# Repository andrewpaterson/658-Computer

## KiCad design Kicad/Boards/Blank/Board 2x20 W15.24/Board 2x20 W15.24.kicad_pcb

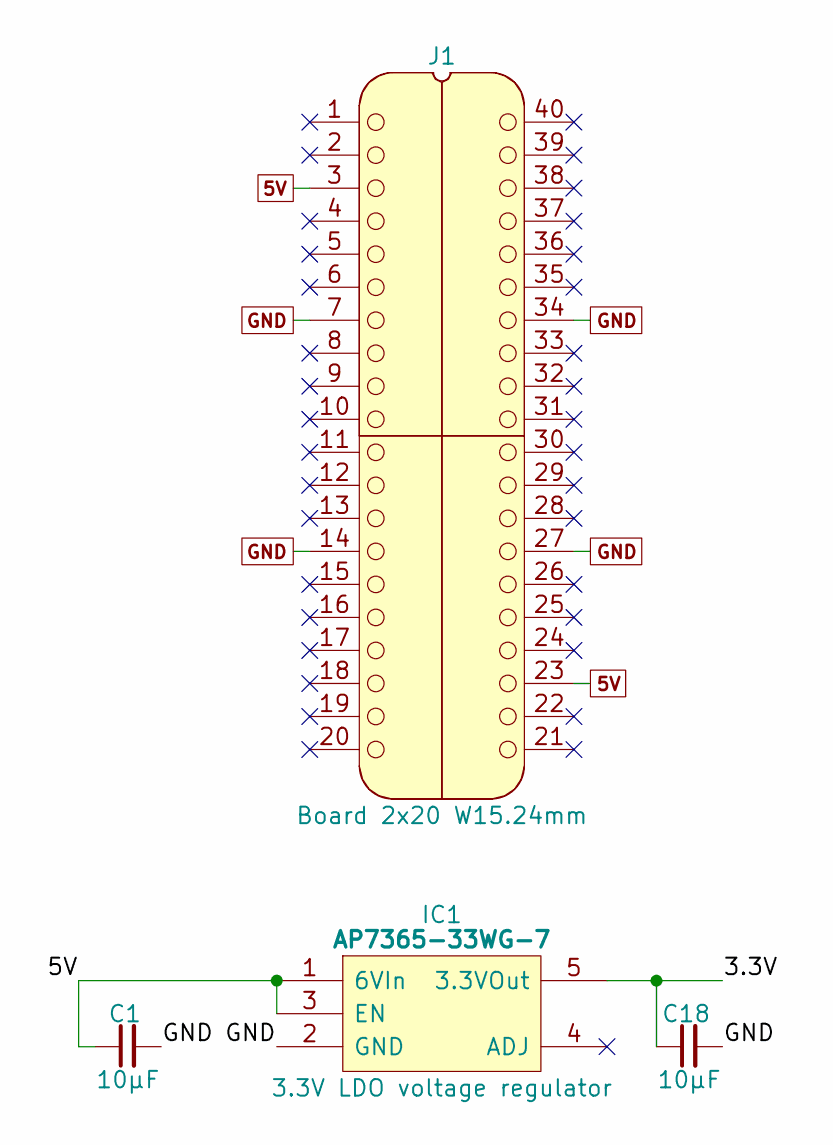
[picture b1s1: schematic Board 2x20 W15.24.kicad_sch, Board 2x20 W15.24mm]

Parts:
C1, C18: 10µF; C_0805
IC1: AP7365-33WG-7; SOT95P285X130-5N; Manufacturer_Part_Number AP7365-33WG-7; Mouser Part Number 621-AP7365-33WG-7
J1: Board 2x20 W15.24mm; DIP-40_Board_W15.24mm

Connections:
5V: C1.1, IC1.1 (6VIn), IC1.3 (EN), J1.3, J1.23
/3.3V: C18.1, IC1.5 (3.3VOut)
GND: C1.2, C18.2, IC1.2 (GND), J1.7, J1.14, J1.27, J1.34

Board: 2 copper layers, 4 parts (0 on the bottom side), 3 nets, no tracks yet.

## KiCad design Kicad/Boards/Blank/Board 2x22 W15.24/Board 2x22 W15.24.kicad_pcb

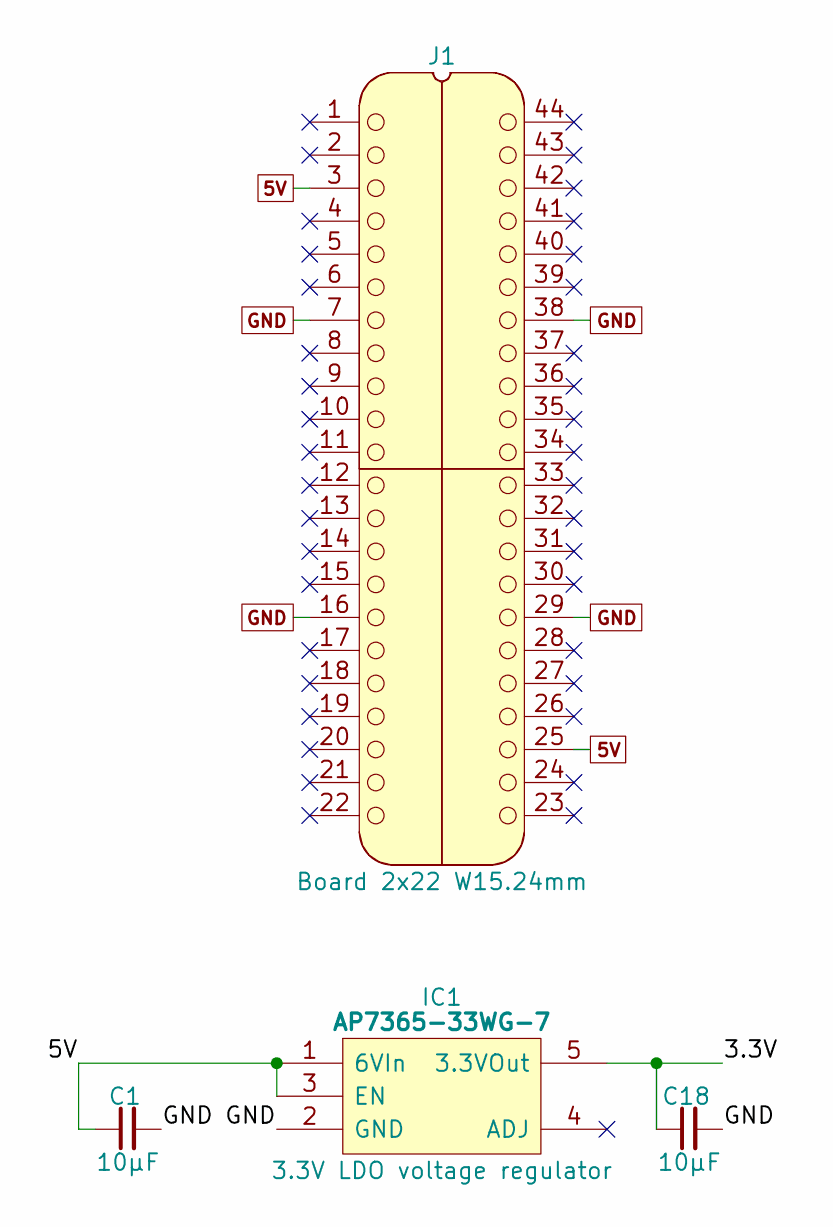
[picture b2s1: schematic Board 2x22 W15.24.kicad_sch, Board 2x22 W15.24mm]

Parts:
C1, C18: 10µF; C_0805
IC1: AP7365-33WG-7; SOT95P285X130-5N; Manufacturer_Part_Number AP7365-33WG-7; Mouser Part Number 621-AP7365-33WG-7
J1: Board 2x22 W15.24mm; DIP-44_Board_W15.24mm

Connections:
5V: C1.1, IC1.1 (6VIn), IC1.3 (EN), J1.3, J1.25
/3.3V: C18.1, IC1.5 (3.3VOut)
GND: C1.2, C18.2, IC1.2 (GND), J1.7, J1.16, J1.29, J1.38

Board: 2 copper layers, 4 parts (0 on the bottom side), 3 nets, no tracks yet.

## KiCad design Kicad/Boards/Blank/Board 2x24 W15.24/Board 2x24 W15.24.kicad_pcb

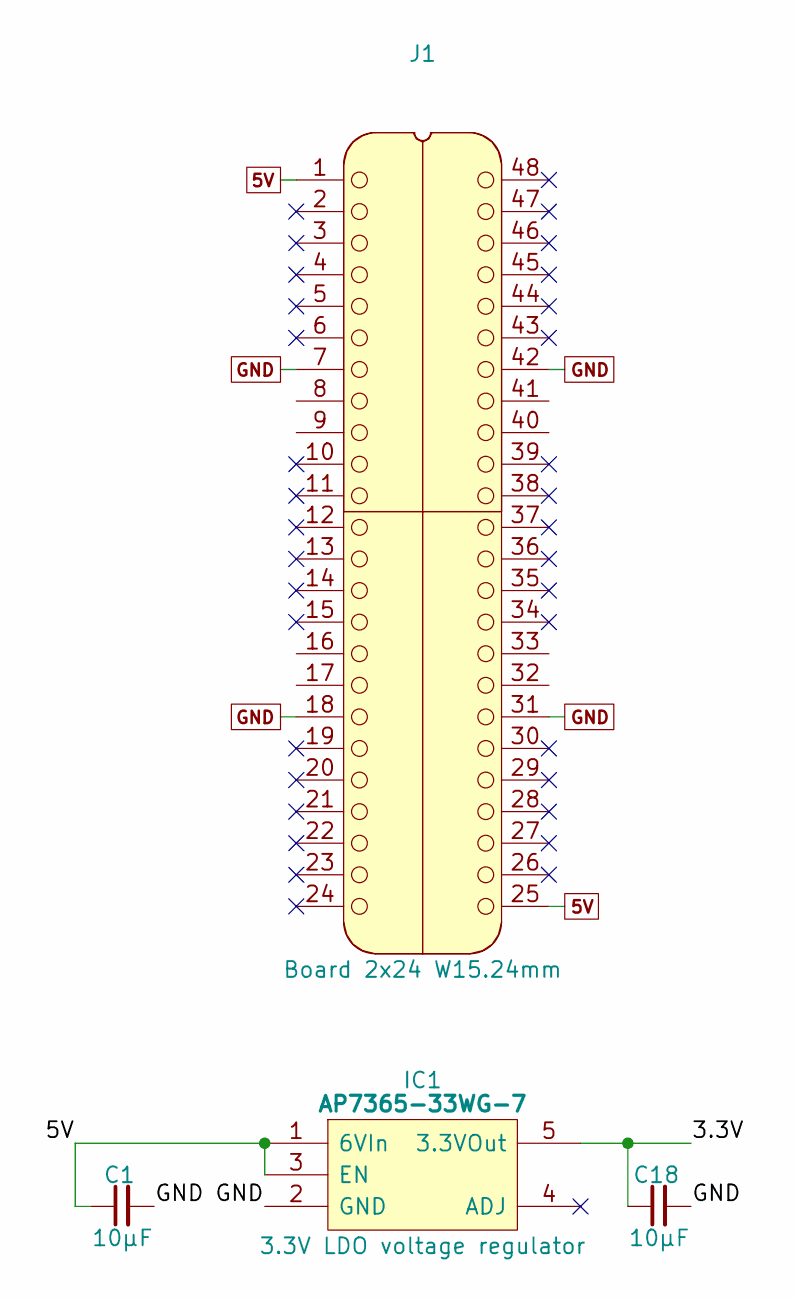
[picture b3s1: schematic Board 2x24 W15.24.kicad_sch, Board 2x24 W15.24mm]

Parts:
C1, C18: 10µF; C_0805
IC1: AP7365-33WG-7; SOT95P285X130-5N; Manufacturer_Part_Number AP7365-33WG-7; Mouser Part Number 621-AP7365-33WG-7
J1: Board 2x24 W15.24mm; DIP-48_Board_W15.24mm

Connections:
5V: C1.1, IC1.1 (6VIn), IC1.3 (EN), J1.1, J1.25
/3.3V: C18.1, IC1.5 (3.3VOut)
GND: C1.2, C18.2, IC1.2 (GND), J1.7, J1.18, J1.31, J1.42

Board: 2 copper layers, 4 parts (0 on the bottom side), 3 nets, no tracks yet.

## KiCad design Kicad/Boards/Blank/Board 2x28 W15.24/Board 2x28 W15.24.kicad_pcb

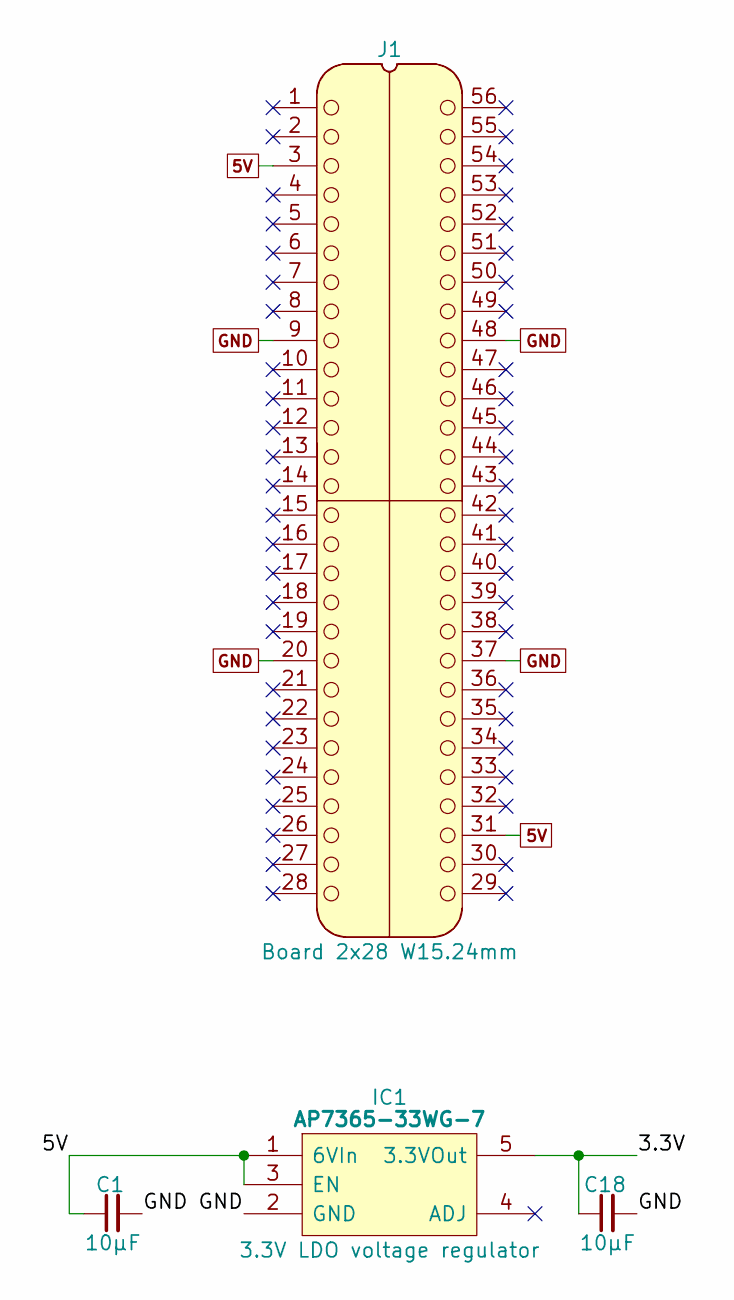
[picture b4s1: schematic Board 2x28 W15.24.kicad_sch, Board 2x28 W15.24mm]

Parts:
C1, C18: 10µF; C_0805
IC1: AP7365-33WG-7; SOT95P285X130-5N; Manufacturer_Part_Number AP7365-33WG-7; Mouser Part Number 621-AP7365-33WG-7
J1: Board 2x28 W15.24mm; DIP-56_Board_W15.24mm

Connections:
5V: C1.1, IC1.1 (6VIn), IC1.3 (EN), J1.3, J1.31
/3.3V: C18.1, IC1.5 (3.3VOut)
GND: C1.2, C18.2, IC1.2 (GND), J1.9, J1.20, J1.37, J1.48

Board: 2 copper layers, 4 parts (0 on the bottom side), 3 nets, no tracks yet.

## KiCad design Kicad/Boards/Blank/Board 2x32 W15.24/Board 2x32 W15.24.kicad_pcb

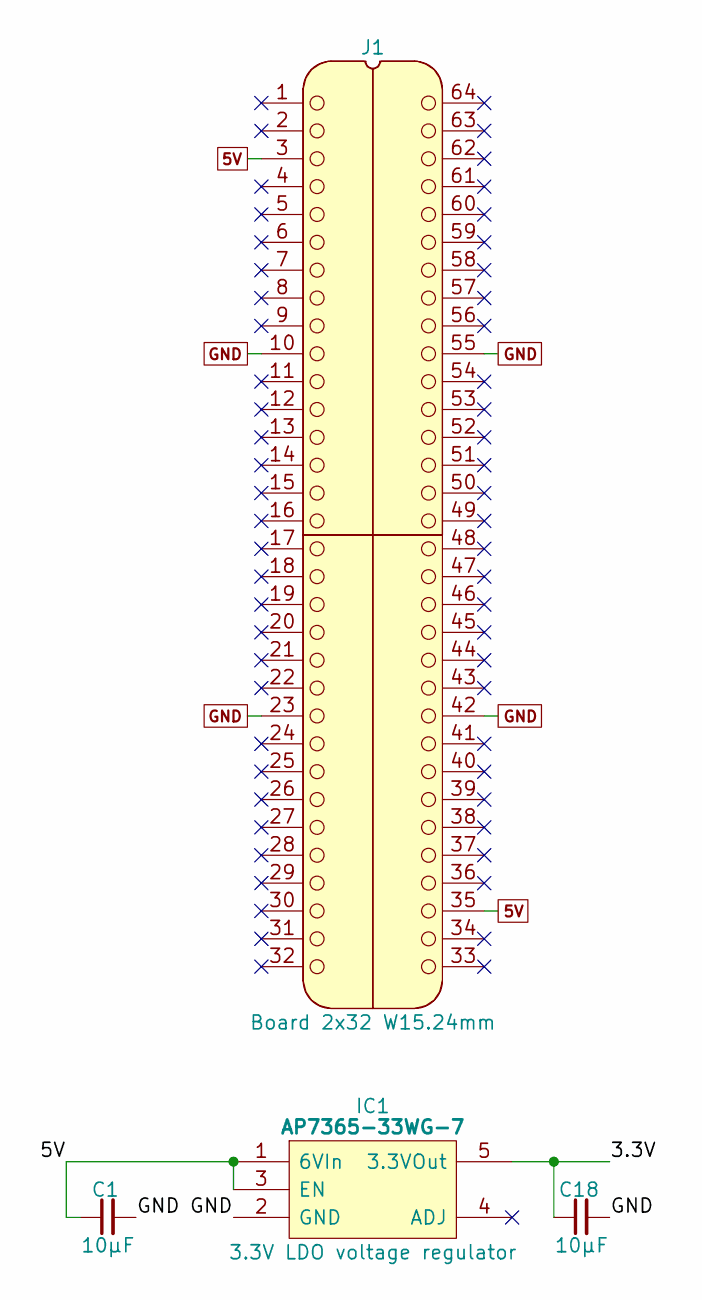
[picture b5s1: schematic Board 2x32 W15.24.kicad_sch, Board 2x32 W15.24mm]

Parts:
C1, C18: 10µF; C_0805
IC1: AP7365-33WG-7; SOT95P285X130-5N; Manufacturer_Part_Number AP7365-33WG-7; Mouser Part Number 621-AP7365-33WG-7
J1: Board 2x32 W15.24mm; DIP-64_Board_W15.24mm

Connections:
5V: C1.1, IC1.1 (6VIn), IC1.3 (EN), J1.3, J1.35
/3.3V: C18.1, IC1.5 (3.3VOut)
GND: C1.2, C18.2, IC1.2 (GND), J1.10, J1.23, J1.42, J1.55

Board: 2 copper layers, 4 parts (0 on the bottom side), 3 nets, no tracks yet.
